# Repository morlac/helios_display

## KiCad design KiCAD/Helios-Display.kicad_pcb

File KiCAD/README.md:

## RESOURCES
 - AM4490N-Datasheet {https://www.analogpowerinc.com/datasheet.php?data1=DS_AM4490N_1A_2}

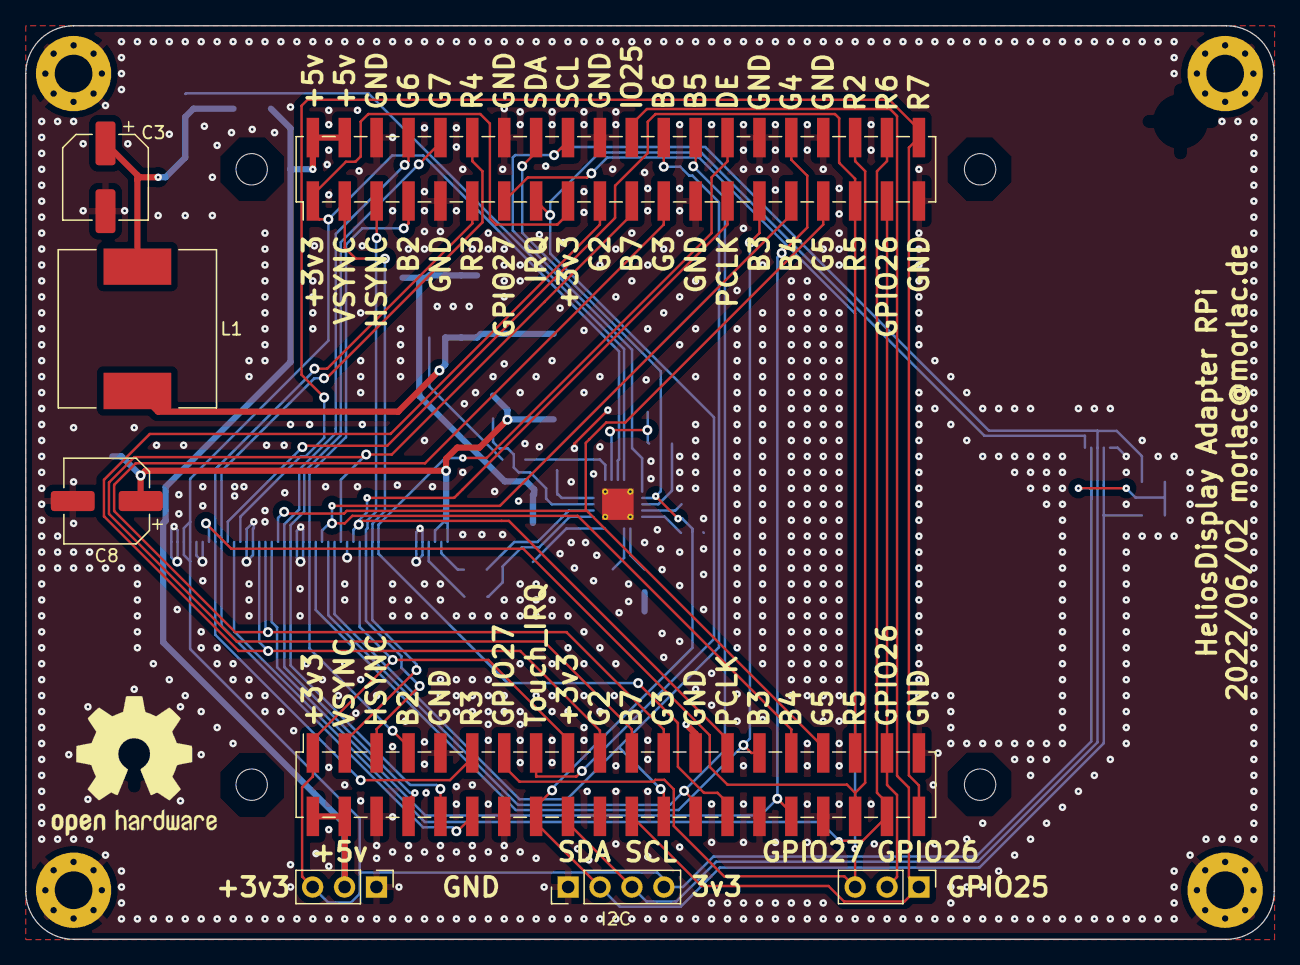
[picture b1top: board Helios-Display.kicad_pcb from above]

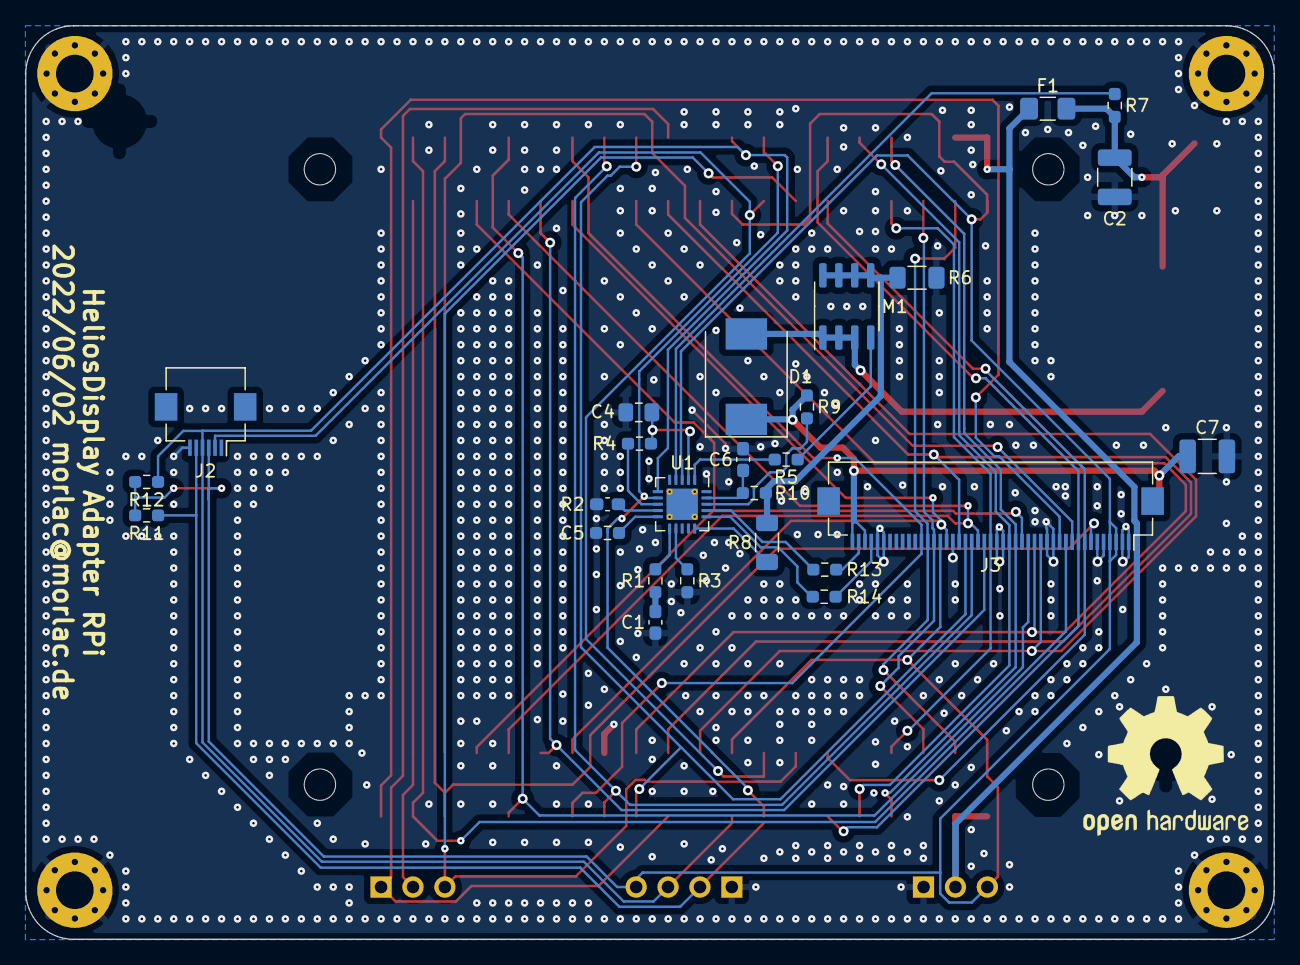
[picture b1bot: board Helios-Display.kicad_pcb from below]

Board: 2 copper layers, 99.4 x 72.7 mm, 44 parts (27 on the bottom side), 52 nets.

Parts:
C1: 470nF; C_0603_1608Metric_Pad1.08x0.95mm_HandSolder
C2: 4.7uF/16V; C_1210_3225Metric_Pad1.33x2.70mm_HandSolder
C3: 220uF/16V; CP_Elec_6.3x3
C4: 0.47uF; C_0805_2012Metric_Pad1.18x1.45mm_HandSolder
C5: 100nF; C_0603_1608Metric_Pad1.08x0.95mm_HandSolder
C6: NC; C_0603_1608Metric_Pad1.08x0.95mm_HandSolder
C7: 4.7uF/25V; C_1210_3225Metric_Pad1.33x2.70mm_HandSolder
C8: 22uF/25V; CP_Elec_6.3x3
D1: B360; D_SMC
F1: Fuse; Fuse_1206_3216Metric_Pad1.42x1.75mm_HandSolder
H1, H2, H3, H4: MountingHole_Pad; MountingHole_3mm_Pad_Via
H5, H6, H7, H8: MountingHoleRaspi; MountingHole_2.5mm
J1, J8: Raspberry_Pi_2_3; PinHeader_2x20_P2.54mm_Vertical_SMD
J2: FFC_ST1633 (Touch); Hirose_FH12-6S-0.5SH_1x06-1MP_P0.50mm_Horizontal
J3: FFC_LCD; Hirose_FH12-45S-0.5SH_1x45-1MP_P0.50mm_Horizontal
J4: Power; PinHeader_1x03_P2.54mm_Vertical
J6: I2C; PinHeader_1x04_P2.54mm_Vertical
J7: GPIO; PinHeader_1x03_P2.54mm_Vertical
L1: 33uH/3.5A; L_12x12mm_H8mm
M1: AM4490N; SOIC-8_3.9x4.9mm_P1.27mm
OSHW_F: OSHW-Logo2_14.6x12mm_SilkScreen
OSJW_B: OSHW-Logo2_14.6x12mm_SilkScreen
R1: 270; R_0603_1608Metric_Pad0.98x0.95mm_HandSolder
R2, R4: 100k; R_0603_1608Metric_Pad0.98x0.95mm_HandSolder
R3: R; R_0603_1608Metric_Pad0.98x0.95mm_HandSolder
R5: 10; R_0603_1608Metric_Pad0.98x0.95mm_HandSolder
R6: 50m; R_1206_3216Metric_Pad1.30x1.75mm_HandSolder
R7, R9, R10, R13, R14: 0; R_0603_1608Metric_Pad0.98x0.95mm_HandSolder
R8: NC; R_1206_3216Metric_Pad1.30x1.75mm_HandSolder
R11, R12: 50; R_0603_1608Metric_Pad0.98x0.95mm_HandSolder
U1: MP3385A; QFN-20-1EP_4x4mm_P0.5mm_EP2.5x2.5mm_ThermalVias

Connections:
+3V3: J1.1 (3V3), J1.17 (3V3), J2.3, J3.3, J3.4, J3.31, J4.3, J6.4, J8.1 (3V3), J8.17 (3V3), R11.2, R12.2, U1.3 (EN)
+5V: F1.1, J1.2 (5V), J1.4 (5V), J4.2, J8.2 (5V), J8.4 (5V)
/GPIO25: J1.22 (GPIO25), J7.1, J8.22 (GPIO25)
/GPIO26: J1.37 (GPIO26), J7.2, J8.37 (GPIO26)
/GPIO27: J1.13 (GPIO27), J7.3, J8.13 (GPIO27)
/GPIO_SCL: J1.18 (GPIO24), J2.4, J6.3, J8.18 (GPIO24), R12.1, U1.6 (SCL)
/GPIO_SDA: J1.16 (GPIO23), J2.5, J6.2, J8.16 (GPIO23), R11.1, U1.7 (SDA)
/LCD_B_{2}: J1.7 (GCLK0/GPIO4), J3.23, J8.7 (GCLK0/GPIO4)
/LCD_B_{3}: J1.29 (GCLK1/GPIO5), J3.24, J8.29 (GCLK1/GPIO5)
/LCD_B_{4}: J1.31 (GCLK2/GPIO6), J3.25, J8.31 (GCLK2/GPIO6)
/LCD_B_{5}: J1.26 (~CE1/GPIO7), J3.26, J8.26 (~CE1/GPIO7)
/LCD_B_{6}: J1.24 (~CE0/GPIO8), J3.27, J8.24 (~CE0/GPIO8)
/LCD_B_{7}: J1.21 (MISO0/GPIO9), J3.28, J8.21 (MISO0/GPIO9)
/LCD_DE: J1.28 (ID_SC/GPIO1), J3.34, J8.28 (ID_SC/GPIO1)
/LCD_G_{2}: J1.19 (MOSI0/GPIO10), J3.15, J8.19 (MOSI0/GPIO10)
/LCD_G_{3}: J1.23 (SCLK0/GPIO11), J3.16, J8.23 (SCLK0/GPIO11)
/LCD_G_{4}: J1.32 (PWM0/GPIO12), J3.17, J8.32 (PWM0/GPIO12)
/LCD_G_{5}: J1.33 (PWM1/GPIO13), J3.18, J8.33 (PWM1/GPIO13)
/LCD_G_{6}: J1.8 (GPIO14/TXD), J3.19, J8.8 (GPIO14/TXD)
/LCD_G_{7}: J1.10 (GPIO15/RXD), J3.20, J8.10 (GPIO15/RXD)
/LCD_HSYNC: J1.5 (SCL/GPIO3), J3.32, J8.5 (SCL/GPIO3)
/LCD_LED_A1: C7.1, C8.1, D1.1 (K), J3.43, J3.45, R9.2
/LCD_LED_C1: J3.42, R14.2
/LCD_LED_C2: J3.44, R13.2
/LCD_PCLK: J1.27 (ID_SD/GPIO0), J3.30, J8.27 (ID_SD/GPIO0)
/LCD_R_{2}: J1.36 (GPIO16), J3.7, J8.36 (GPIO16)
/LCD_R_{3}: J1.11 (GPIO17), J3.8, J8.11 (GPIO17)
/LCD_R_{4}: J1.12 (GPIO18/PWM0), J3.9, J8.12 (GPIO18/PWM0)
/LCD_R_{5}: J1.35 (GPIO19/MISO1), J3.10, J8.35 (GPIO19/MISO1)
/LCD_R_{6}: J1.38 (GPIO20/MOSI1), J3.11, J8.38 (GPIO20/MOSI1)
/LCD_R_{7}: J1.40 (GPIO21/SCLK1), J3.12, J8.40 (GPIO21/SCLK1)
/LCD_VSYNC: J1.3 (SDA/GPIO2), J3.33, J8.3 (SDA/GPIO2)
/ST1633_IRQ: J1.15 (GPIO22), J2.2, J8.15 (GPIO22)
/VCC: C4.2, R4.1, U1.2 (VCC)
GNDA: C1.2, C2.2, C3.2, C4.1, C5.2, C6.2, C7.2, C8.2, H1.1, H2.1, H3.1, H4.1, J1.6 (GND), J1.9 (GND), J1.14 (GND), J1.20 (GND), J1.25 (GND), J1.30 (GND), J1.34 (GND), J1.39 (GND), J2.6, J3.1, J3.2, J3.5, J3.6, J3.13, J3.14, J3.21, J3.22, J3.29, J3.40, J3.41, J4.1, J6.1, J8.6 (GND), J8.9 (GND), J8.14 (GND), J8.20 (GND), J8.25 (GND), J8.30 (GND), J8.34 (GND), J8.39 (GND), R2.1, R3.2, R6.2, U1.21 (GND)
unnamed: C1.1, R1.2
unnamed: C2.1, C3.1, F1.2, L1.1, R7.1
unnamed: C5.1, U1.9 (LPF)
unnamed: C6.1, R10.1, U1.19 (IS)
unnamed: D1.2 (A), L1.2, M1.1 (D), M1.2 (D), M1.3 (D)
unnamed: M1.4 (G), R5.2
unnamed: M1.5 (S), M1.6 (S), M1.7 (S), M1.8 (S), R6.1, R8.2, R10.2
unnamed: R1.1, U1.11 (COMP)
unnamed: R2.2, U1.10 (OSC)
unnamed: R3.1, U1.12 (ISET)
unnamed: R4.2, U1.8 (FT)
unnamed: R5.1, U1.1 (DRV)
unnamed: R7.2, U1.4 (VIN)
unnamed: R8.1, U1.15 (PGND)
unnamed: R14.1, U1.16 (LED2)
unnamed: R13.1, U1.17 (LED1)
unnamed: R9.1, U1.18 (OVP)

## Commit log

2022-02-08 inital data commit
2022-03-13 added adapter-holder
2022-03-15 updated some measures
2022-04-18 KiCAD initial commit
2022-06-07 added .gitignore
2022-06-07 updated FreeCAD files
2022-06-07 updated KiCAD files
2022-06-07 current version of Helios-Display.wrl
